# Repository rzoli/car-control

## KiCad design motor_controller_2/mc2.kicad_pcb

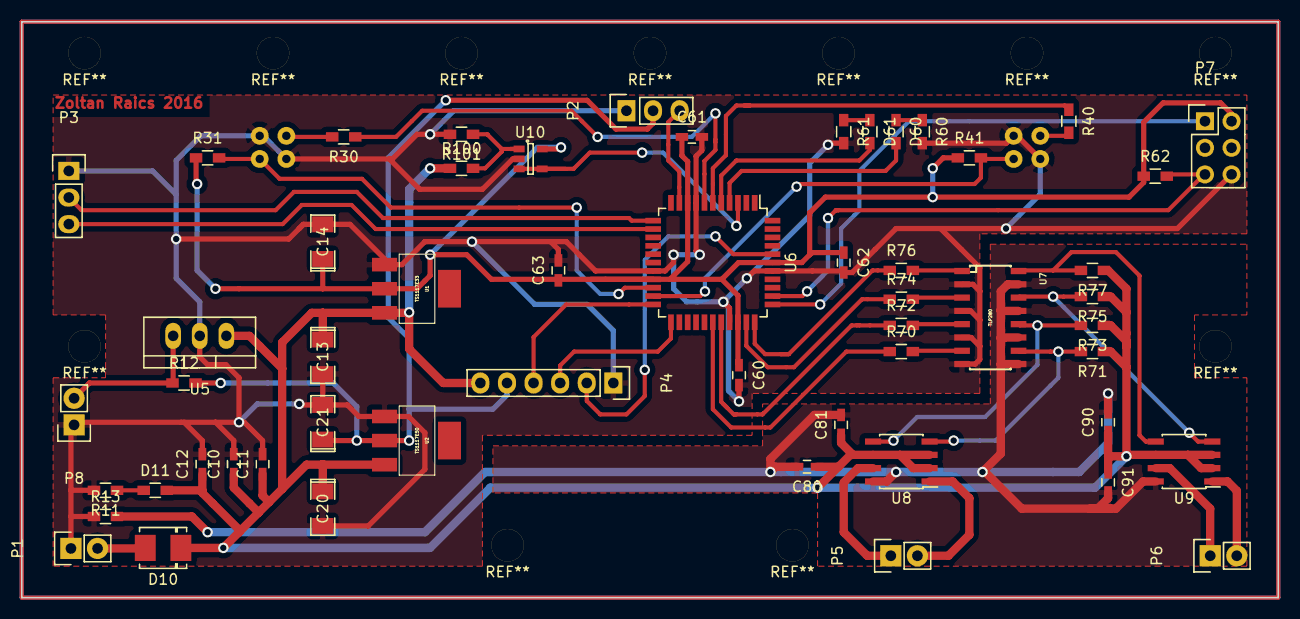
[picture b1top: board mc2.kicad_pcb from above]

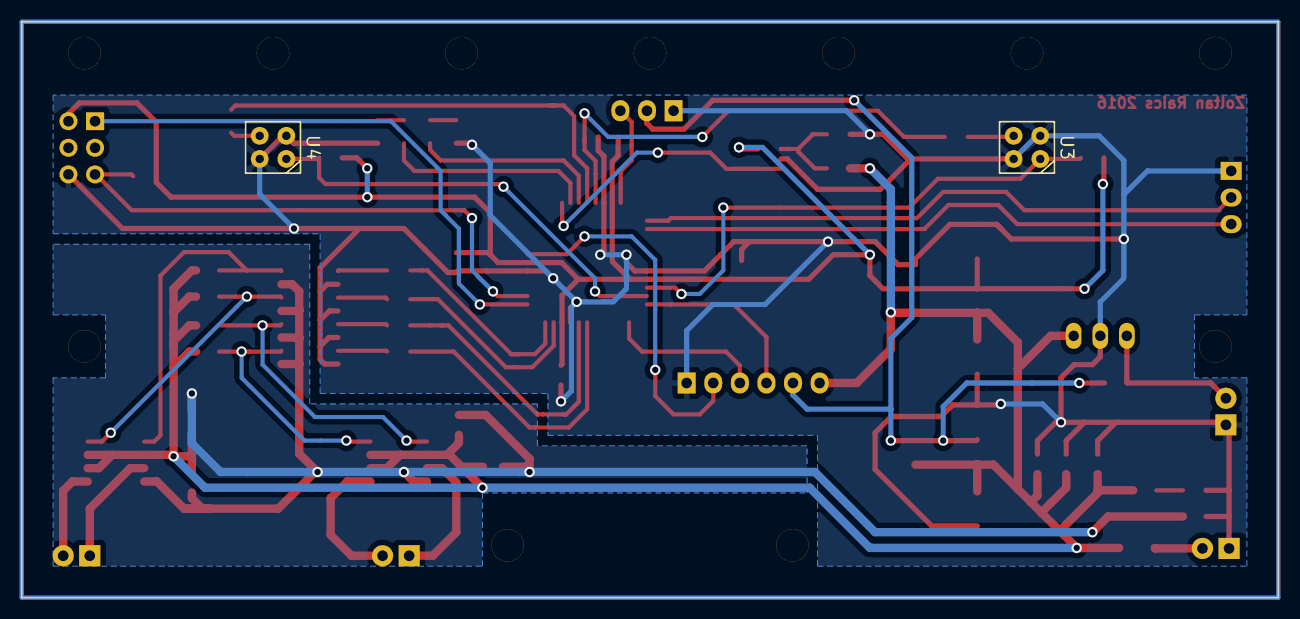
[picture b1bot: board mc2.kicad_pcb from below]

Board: 2 copper layers, 120.0 x 55.0 mm, 57 parts (2 on the bottom side), 44 nets.

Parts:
C10: 47 pF; C_0603_HandSoldering
C11, C60, C61, C62, C63, C81, C91: 100 nF; C_0603_HandSoldering
C12: 1 uF; C_0603_HandSoldering
C13, C14, C20, C21: 10 uF; SMD-1206_Pol
C80, C90: 10 nF; C_0603_HandSoldering
D10: SS24; DO-214BA
D11, D60, D61: LED; R_0603_HandSoldering
P1: Battery; Pin_Header_Straight_1x02
P2: Servo; Pin_Header_Straight_1x03
P3: Uart; Pin_Header_Straight_1x03
P4: Ultrasound; Pin_Header_Straight_1x06
P5: Motor left; Pin_Header_Straight_1x02
P6: Motor right; Pin_Header_Straight_1x02
P7: ISP; Pin_Header_Straight_2x03
P8: RPi 5V; Pin_Header_Straight_1x02
R11, R30, R40, R60, R61, R70, R72, R74, R76: 300; R_0603_HandSoldering
R12, R13: 0; R_0603_HandSoldering
R31, R41, R71, R73, R75, R77: 10k; R_0603_HandSoldering
R62: 4k7; R_0603_HandSoldering
R100: 510k; R_0603_HandSoldering
R101: 39k; R_0603_HandSoldering
U1: TS1117E33; SOT-223
U2: TS1117E50; SOT-223
U3, U4: PC817; OPB606
U5: R-78BXX; TO-220_Neutral123_Vertical
U6: ATXMEGA32A4U-A; TQFP-44_10x10mm_Pitch0.8mm
U7: TLP280; SOIC16
U8, U9: BD6221F-E2; SOIC-8_3.9x4.9mm_Pitch1.27mm
U10: ts321; SOT-23-5

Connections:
+3V3: C14.1, C60.1, C61.1, C62.1, C63.1, P7.2, R31.1, R41.1, R62.1, U1.2, U6.9, U6.19, U6.31, U6.39, U10.5
+5V: C21.1, P2.2, P4.5, R12.2, U2.2
+5VD: P8.2, R12.1, U5.3
+BATT: C10.1, C11.1, C12.1, C13.1, C20.1, C80.1, C81.1, C90.1, C91.1, D10.1, D11.2, P4.6, R71.1, R73.1, R75.1, R77.1, R100.1, U1.3, U2.3, U5.1, U8.2, U8.3, U8.6, U9.2, U9.3, U9.6
/ADC: P4.2, U6.40
/ADC_Vbatt: U6.3, U10.3, U10.4
/Forward_left: R70.1, U6.28
/Forward_left_i: R71.2, U7.10, U8.4
/Forward_right: R74.1, U6.32
/Forward_right_i: R75.2, U7.14, U9.4
/IR_left: R30.1, U6.7
/IR_right: R40.1, U6.6
/LED0: D60.2, U6.4
/LED1: D61.2, U6.5
/Motor_left_out1: P5.2, U8.1
/Motor_left_out2: P5.1, U8.7
/Motor_right_out1: P6.2, U9.1
/Motor_right_out2: P6.1, U9.7
/PDI_Clock: P7.5, R62.2, U6.35
/PDI_Data: P7.1, U6.34
/Pulse_in: P4.3, U6.23
/Pulse_out: P4.4, U6.22
/RX: P3.2, U6.12
/Reverse_left: R72.1, U6.29
/Reverse_left_i: R73.2, U7.12, U8.5
/Reverse_right: R76.1, U6.33
/Reverse_right_i: R77.2, U7.16, U9.5
/Rpm_left: R31.2, U3.4, U6.20
/Rpm_right: R41.2, U4.4, U6.21
/Servo_pwm: P2.3, U6.10
/TX: P3.3, U6.13
GND: C10.2, C11.2, C12.2, C13.2, C14.2, C20.2, C21.2, C60.2, C61.2, C62.2, C63.2, P1.1, P2.1, P3.1, P4.1, P7.6, P8.1, R11.2, R13.1, R60.2, R61.2, R101.2, U1.1, U2.1, U3.2, U3.3, U4.2, U4.3, U5.2, U6.8, U6.18, U6.30, U6.38, U7.2, U7.4, U7.6, U7.8, U10.2
GNDPWR: C80.2, C81.2, C90.2, C91.2, R13.2, U7.9, U7.11, U7.13, U7.15, U8.8, U9.8
unnamed: D10.2, P1.2
unnamed: D11.1, R11.1
unnamed: D60.1, R60.1
unnamed: D61.1, R61.1
unnamed: R30.2, U3.1
unnamed: R40.2, U4.1
unnamed: R70.2, U7.7
unnamed: R72.2, U7.5
unnamed: R74.2, U7.3
unnamed: R76.2, U7.1
unnamed: R100.2, R101.1, U10.1

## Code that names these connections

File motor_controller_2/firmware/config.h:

#define F_CPU 2000000UL
#define BAUD 115200
#define RED_LED 0
#define GREEN_LED 1
#define IR_RIGHT 2
#define IR_LEFT 3
#define SET_GREEN_LED  PORTB.OUTSET = 1<<GREEN_LED
#define CLEAR_GREEN_LED  PORTB.OUTCLR = 1<<GREEN_LED
#define SET_RED_LED  PORTB.OUTSET = 1<<RED_LED
#define CLEAR_RED_LED  PORTB.OUTCLR = 1<<RED_LED

#define F_PWM 12000UL
#define PWM_PRESCALER 1
#define PWM_PERIOD_REGISTER_VALUE F_CPU/(F_PWM*PWM_PRESCALER)-1

#define RPM_LEFT_PIN 0
#define RPM_RIGHT_PIN 1

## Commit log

2013-10-05 Initial commit: firmware contains serial port communication, pwm control, make script and basic test script
2013-10-07 input capture and echo command implemented but not tested
2013-10-09 command interface with unittests - working, introducing unittest usage in firmware test is in progress
2013-10-09 development board schematic added
2014-05-29 blue led renamed to red
2014-11-08 command protocol class (tested only on x86)
2014-11-08 migration to c++ started
2014-11-09 migrating to c++: communication class is repsonsible for sending debug strings over uart
2014-11-13 usart data ponter is not passed to Comm class but read as a global variable, command parsing works on motor driver board
2014-11-26 command protocol updated (not tested)
2014-11-26 command parser/function caller moved to one class
2014-12-15 command interface and setting pwm from host works now
2015-02-23 set led command implemented, tests for motor control commands
2015-02-23 tester-motor controller serial port communication is logged
2015-05-15 gearbox speed analysis
2015-05-18 motor can be moved to forward direction
2015-05-19 remote control interface sketch
2015-05-19 rpm analysis optimization
2015-05-19 remote control can catch all errors and displayed on gui
2015-05-19 gitignore updated
2015-05-22 minor bugfix
2015-05-23 wheel encoder template drawer
2015-05-23 logfile is periodically update on screen, led control (not tested)
2015-08-07 parameter update sent over serial port
2015-08-09 images from remote rpi displayed on gui
2015-08-09 pwm control refactored
2015-10-26 arduino oscilosscope initial version
2015-10-28 start/stop button added
2015-10-30 scope timing fixed
2015-10-30 adc init (not ready)
2015-11-09 arduino scope: ported to uno board (not tested)
2015-11-10 bugfix
2015-11-11 switch between analog and digital modes, timing of analog input is fixed
2015-11-28 voltage and wheel modes added to gui (not tested)
2015-11-30 read adc (not tested)
2015-12-06 ADC readout from microcontroller, motor control works from GUI
2015-12-06 Load adc factory calibration
2015-12-06 Stop motor command
2015-12-06 icon added
2016-01-02 navigation baed on ceiling markers
2016-02-13 rpi camera streamer
2016-02-13 Unused code removed
2016-02-13 make update
2016-02-15 set motor voltages with one command, motion control shortcuts
2016-03-25 motor controller pcb schematic initial version
2016-03-25 renaming schematic
2016-03-28 printable wheel encoder generator
2016-04-01 encoder wheel modified
2016-04-01 encoder wheel: second pattern added
2016-04-01 encoder wheel updated
2016-04-04 optocoupler and motor driver ic added to schematic
2016-04-10 servo connectors added to schematics
2016-04-11 5 V power supply added
2016-04-13 encoder barrel
2016-04-13 barrel encoder wheel fixed
2016-04-13 microcontroller pins assigned
2016-04-15 footprint and symbol library added
2016-04-15 unnecessary files removed
2016-04-16 components labeled
2016-04-16 motor controller schematic can be imported to pcb
2016-08-10 Kicad design
2016-08-10 Behavioral wheel encoder settings
2016-08-28 geda pcb/sch designs removed
2016-08-28 motor controller schematics redrawn in Kicad
2016-08-29 footprints assigned (not ready)
2016-08-30 footprint assignments (not ready)
2016-09-03 all footprints assigned
2016-09-10 footprints finalized
2016-09-18 component layout of motor controller
2016-09-22 pcb wiring (not ready)
2016-09-23 component pins checked
2016-09-27 pcb wiring done
2016-09-28 mounting holes for servo added
2016-10-18 pcb design finalized
2017-02-21 motor vezerlo firmware ujrastrukuralva
2017-02-21 ultrasound scanner gui es firmware, motor vezerlo panel gyartasi fileok veglegesitve
2017-02-24 parancskezelo mukodik par alapveto paranccsal
2017-02-25 Ultrahangos radarkep megjelenites, mentes
2017-03-08 microsecond timer, reset command works, pwm control and batt voltage read (not tested)
2017-03-12 detect close object in ultrasound radar map
2017-03-16 navigation stimulation
2017-03-16 pwm modulacio mukodik, adc kalibracio
2017-06-25 remote control can move motors
2017-06-28 vehicle motion commands
2019-09-14 Read rpm sensors using external interrupts (not tested)
2019-11-23 step counter works
2019-11-30 Step measurement, goto command, pulse width measurement for ultrasound (not tested)
2020-06-10 Python3 compatibility, communication to vehicle via socket, ultrasound distance measurement
